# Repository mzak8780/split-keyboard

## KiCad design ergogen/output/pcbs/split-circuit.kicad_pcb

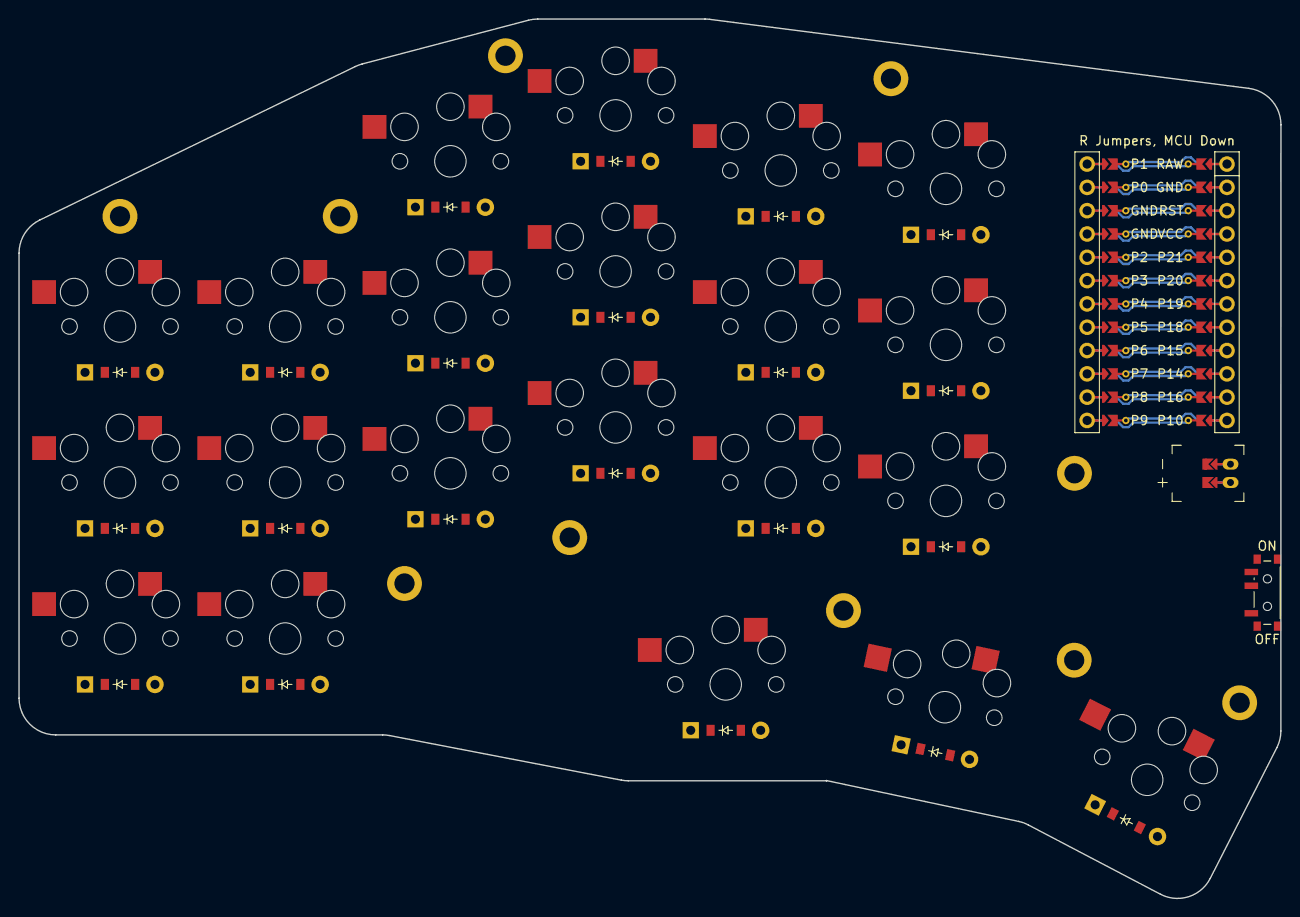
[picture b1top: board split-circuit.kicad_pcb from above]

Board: 2 copper layers, 137.5 x 95.8 mm, 55 parts (0 on the bottom side), 36 nets.

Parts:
D1, D2, D3, D4, D5, D6, D7, D8, D9, D10, D11, D12, D13, D14, D15, D16, D17, D18, D19, D20, D21: ComboDiode
H1, H2, H3, H4, H5, H6, H7, H8, H9, H10: mounting_hole_plated
JST1: battery_connector_jst_ph_2
MCU1: mcu_nice_nano
PWR1: power_switch_smd_side
S1, S2, S3, S4, S5, S6, S7, S8, S9, S10, S11, S12, S13, S14, S15, S16, S17, S18, S19, S20, S21: PG1350

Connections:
BAT_P: JST1.1, PWR1.1, PWR1.3
GND: JST1.2, MCU1.3, MCU1.4, MCU1.123
JST1_1: JST1.11, JST1.21, JST1.31
JST1_2: JST1.12, JST1.22, JST1.32
P4: MCU1.7, S16.1, S17.1, S18.1, S21.1
P5: MCU1.8, S13.1, S14.1, S15.1, S20.1
P6: MCU1.9, S10.1, S11.1, S12.1, S19.1
P7: MCU1.10, S7.1, S8.1, S9.1
P8: MCU1.11, S4.1, S5.1, S6.1
P9: MCU1.12, S1.1, S2.1, S3.1
P10: D3.1, D6.1, D9.1, D12.1, D15.1, D18.1, MCU1.113
P14: D1.1, D4.1, D7.1, D10.1, D13.1, D16.1, MCU1.115
P15: D19.1, D20.1, D21.1, MCU1.116
P16: D2.1, D5.1, D8.1, D11.1, D14.1, D17.1, MCU1.114
RAW: MCU1.124, PWR1.2
far_thumb: D21.2, S21.2
home_thumb: D20.2, S20.2
index_bottom: D13.2, S13.2
index_home: D14.2, S14.2
index_top: D15.2, S15.2
inner_bottom: D16.2, S16.2
inner_home: D17.2, S17.2
inner_top: D18.2, S18.2
middle_bottom: D10.2, S10.2
middle_home: D11.2, S11.2
middle_top: D12.2, S12.2
near_thumb: D19.2, S19.2
outer_bottom: D1.2, S1.2
outer_home: D2.2, S2.2
outer_top: D3.2, S3.2
pinky_bottom: D4.2, S4.2
pinky_home: D5.2, S5.2
pinky_top: D6.2, S6.2
ring_bottom: D7.2, S7.2
ring_home: D8.2, S8.2
ring_top: D9.2, S9.2

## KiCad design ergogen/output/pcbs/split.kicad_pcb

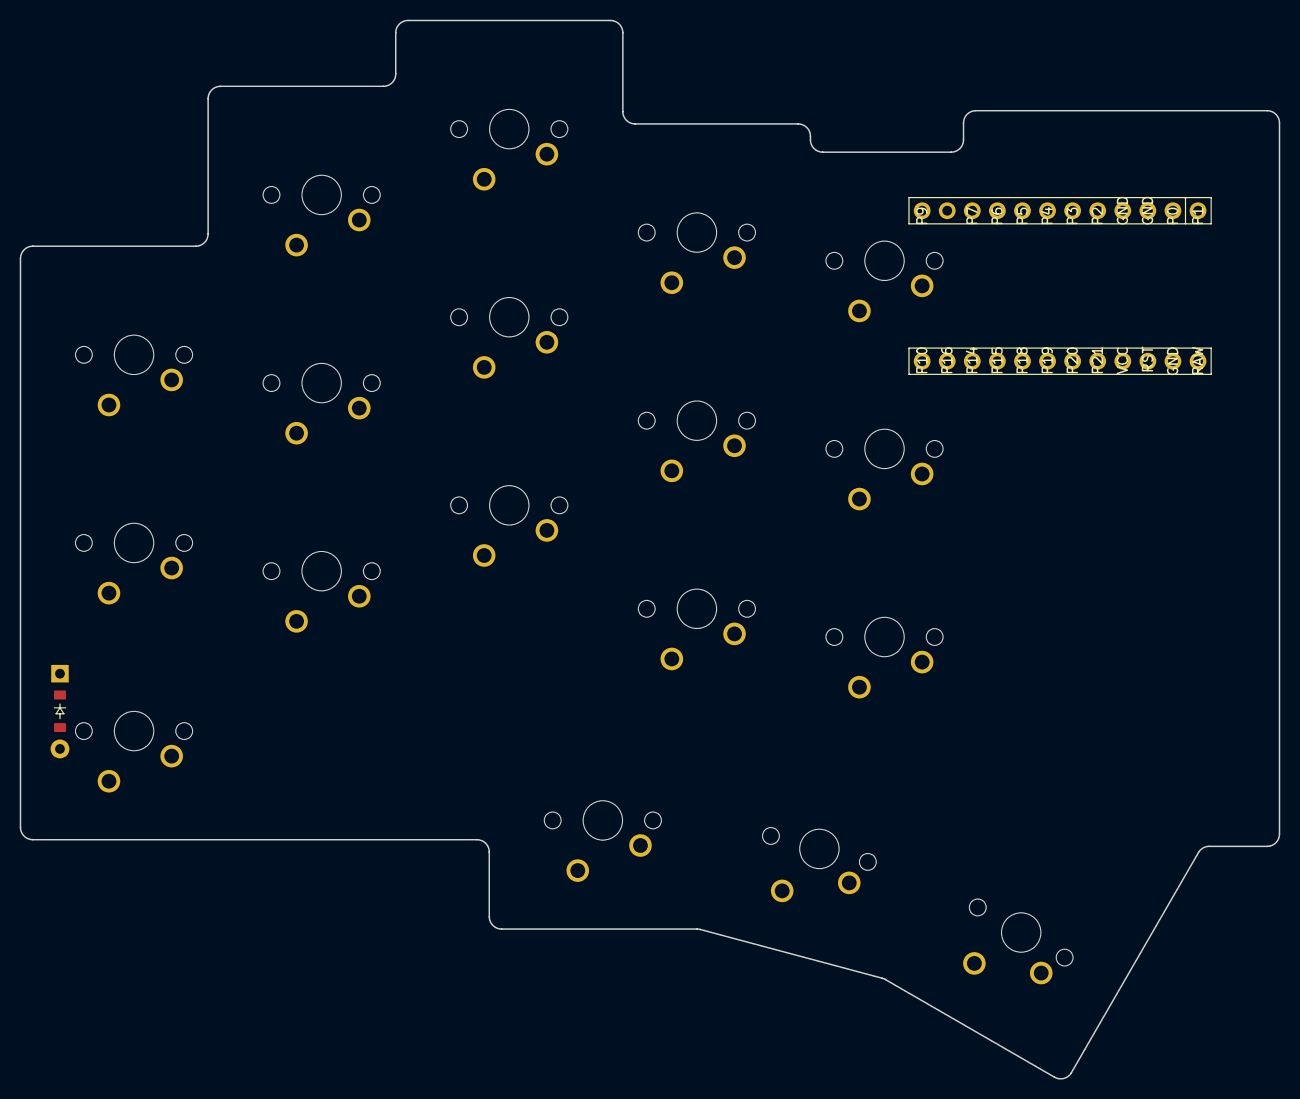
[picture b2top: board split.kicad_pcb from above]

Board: 2 copper layers, 127.5 x 107.2 mm, 20 parts (0 on the bottom side), 5 nets, no tracks yet.

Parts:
D1: ComboDiode
MCU1: mcu_nice_nano
S1, S2, S3, S4, S5, S6, S7, S8, S9, S10, S11, S12, S13, S14, S15, S16, S17, S18: MX

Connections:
GND: MCU1.2, MCU1.21, MCU1.22
P10: MCU1.12, S3.1, S6.1, S9.1, S12.1, S15.1
P14: MCU1.10, S1.1, S4.1, S7.1, S10.1, S13.1
P15: MCU1.9, S16.1, S17.1, S18.1
P16: MCU1.11, S2.1, S5.1, S8.1, S11.1, S14.1

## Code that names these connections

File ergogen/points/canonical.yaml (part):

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    autobind: 10
    skip: false
    asym: both
    colrow: pinky_bottom
    name: matrix_pinky_bottom
    zone: *ref_0
    col: &ref_2
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    autobind: 10
    skip: false
    asym: both
    colrow: pinky_home
    name: matrix_pinky_home
    zone: *ref_0
    col: *ref_2
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    autobind: 10
    skip: false
    asym: both
    colrow: pinky_top
    name: matrix_pinky_top
    zone: *ref_0
    col: *ref_2
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
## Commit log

2024-05-04 feat/initial-commit-ergogen-files
2024-05-04 feat/file-cleanup
2024-05-16 feat/update-ergogen-config-file-and-generate-pcb
